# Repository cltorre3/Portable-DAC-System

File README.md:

# Portable-DAC-System
This is meant to be the repository for all the major electrical files for the portable DAC system.
The ESP32s are programmed in Arduino and the PCB was built in KiCAD

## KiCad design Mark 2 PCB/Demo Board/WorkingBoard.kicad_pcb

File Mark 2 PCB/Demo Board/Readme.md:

This will serve as the location for the demonstration board backup

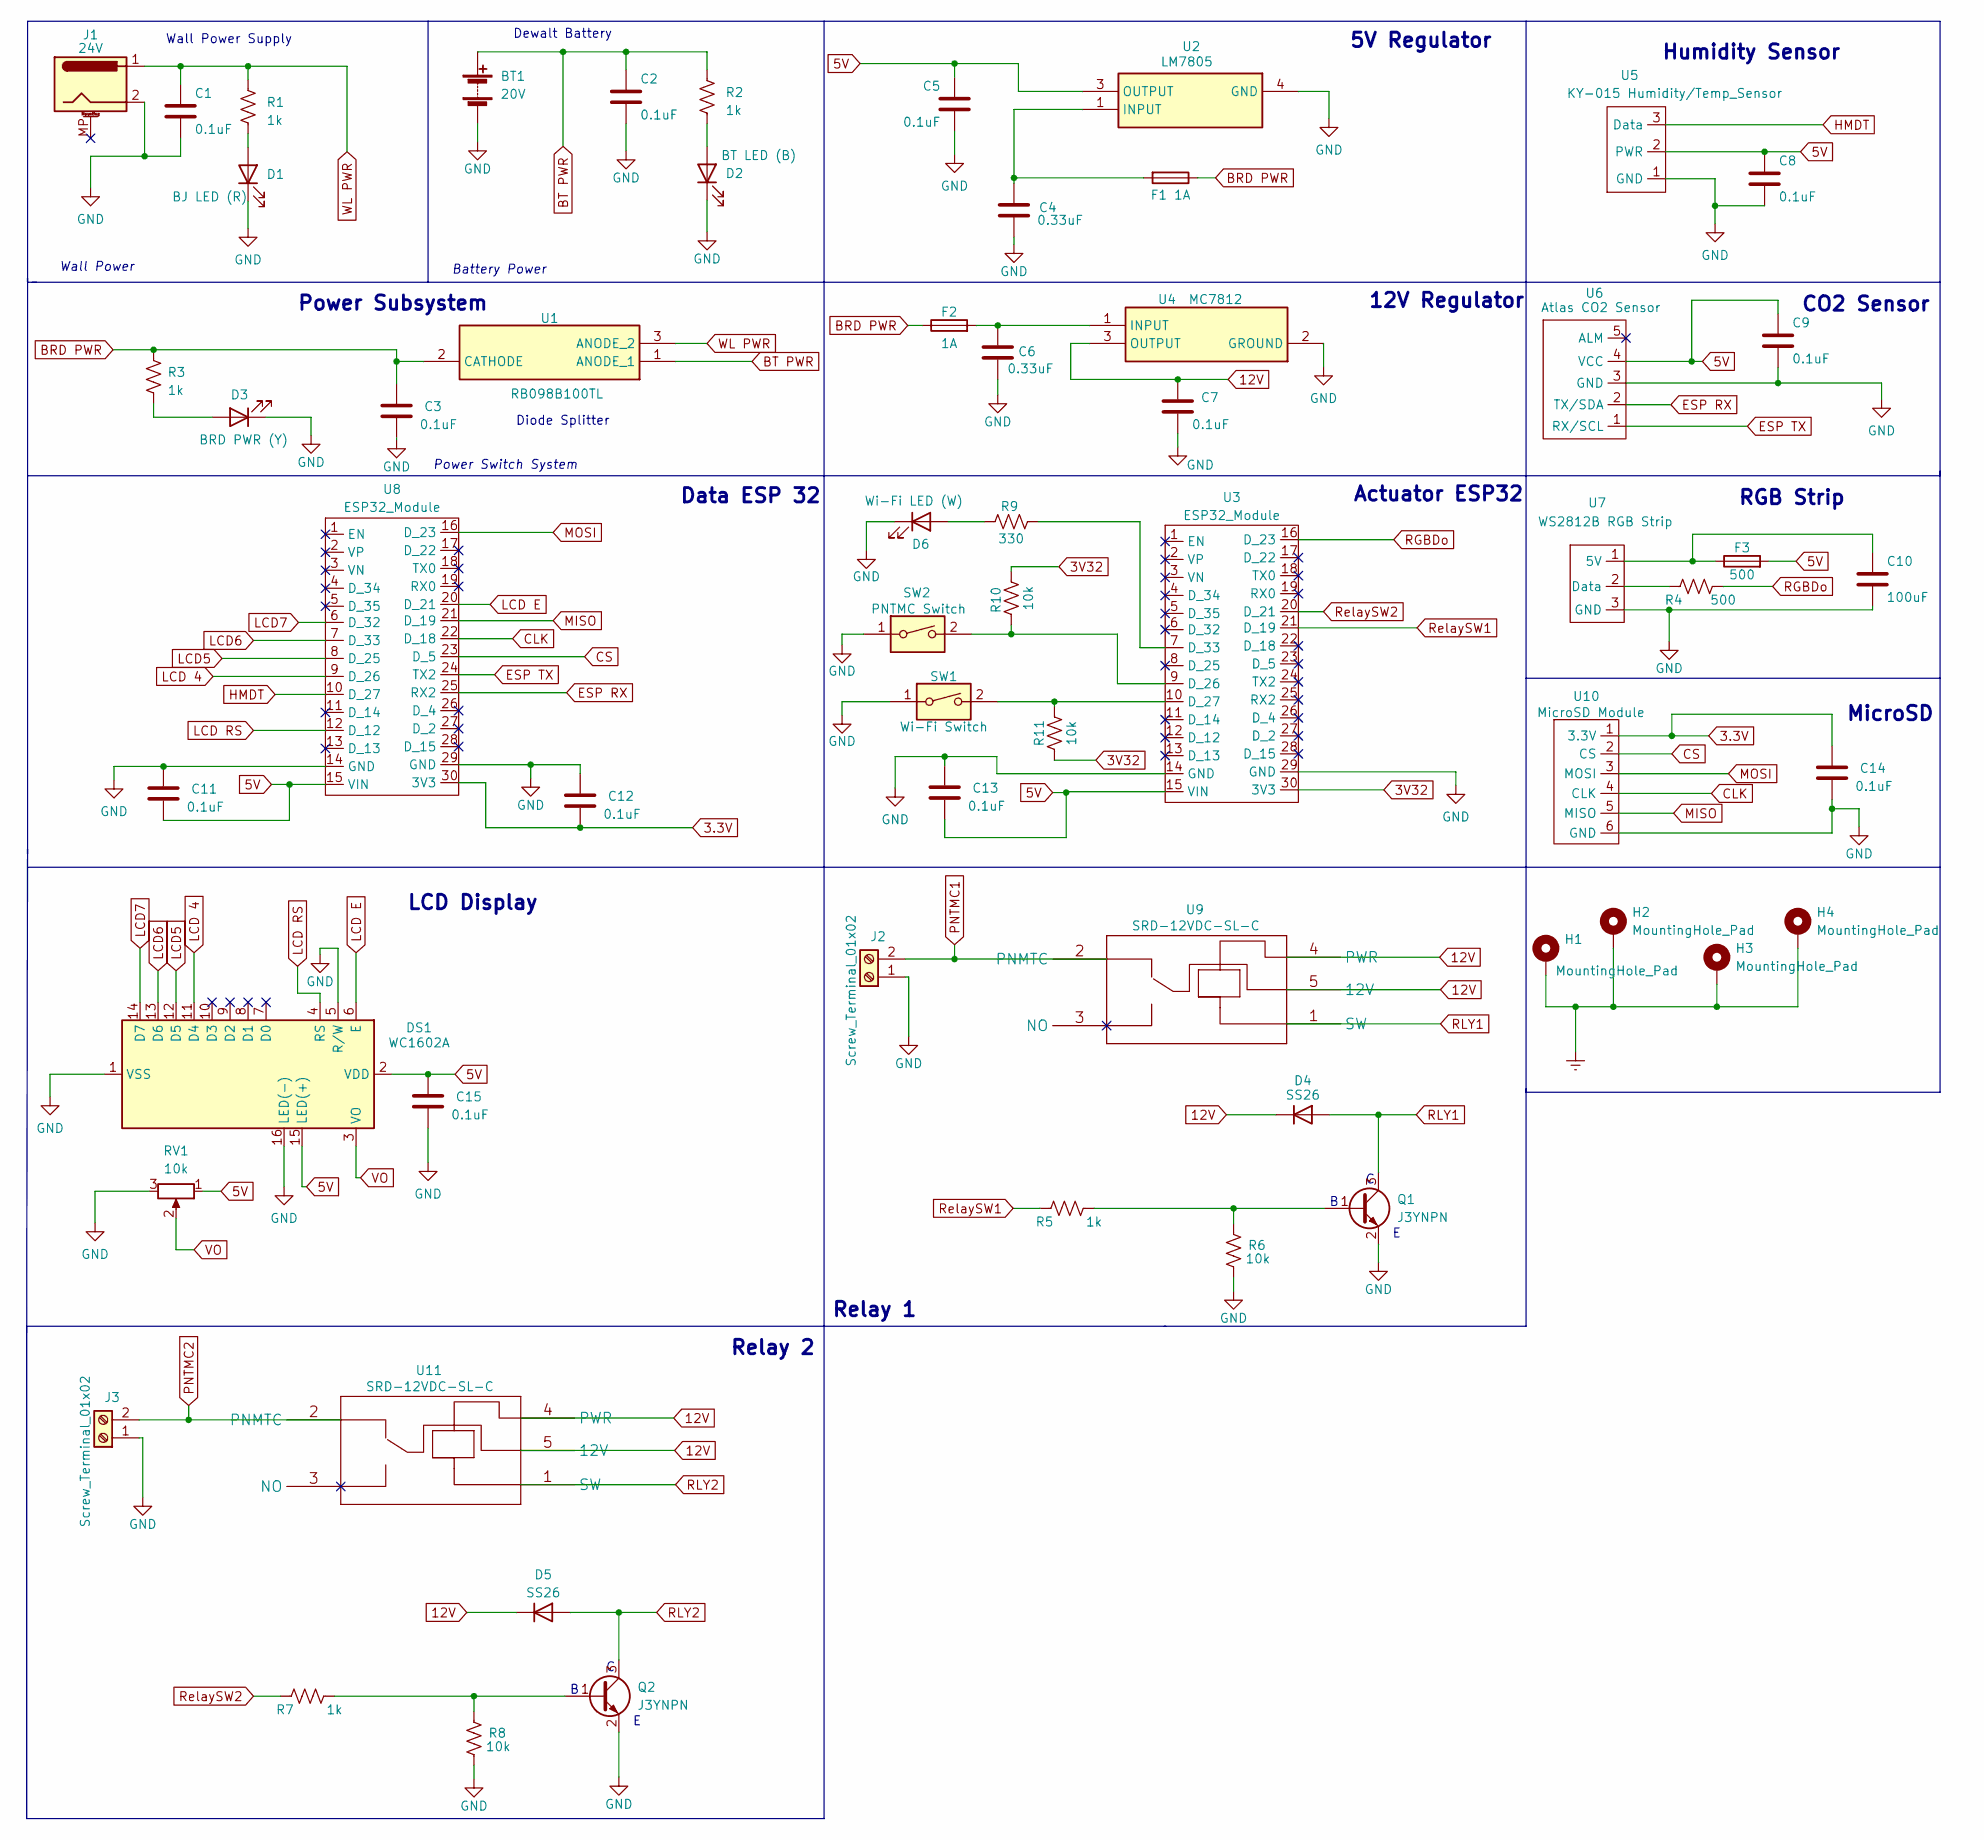
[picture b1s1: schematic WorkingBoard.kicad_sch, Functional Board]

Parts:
BT1: 20V; TerminalBlock_TE_282834-2_1x02_P2.54mm_Horizontal
C1, C2, C3, C5, C7, C8, C9, C11, C12, C13, C14, C15: 0.1uF; C_0805_2012Metric
C4, C6: 0.33uF; C_0805_2012Metric
C10: 100uF; C_0805_2012Metric
D1: BJ LED (R); LED_0805_2012Metric
D2: BT LED (B); LED_0805_2012Metric
D3: BRD PWR (Y); LED_0805_2012Metric
D4, D5: SS26
D6: Wi-Fi LED (W); LED_0805_2012Metric
DS1: WC1602A
F1, F2: 1A; Fuseholder_Cylinder-5x20mm_Schurter_0031_8201_Horizontal_Op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
F3: 500; Fuseholder_Cylinder-5x20mm_Schurter_0031_8201_Horizontal_Op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
H1, H2, H3, H4: MountingHole_Pad; MountingHole_3mm_Pad
J1: 24V; BarrelJack_Horizontal
J2, J3: Screw_Terminal_01x02; TerminalBlock_TE_282834-2_1x02_P2.54mm_Horizontal
Q1, Q2: J3YNPN; SOT-23
R1, R2, R3, R5, R7: 1k; R_0805_2012Metric
R4: 500; R_0805_2012Metric
R6, R8, R10, R11: 10k; R_0805_2012Metric
R9: 330; R_0805_2012Metric
RV1: 10k; Potentiometer_Bourns_3266Y_Vertical
SW1: Wi-Fi Switch; PinHeader_1x02_P2.54mm_Vertical
SW2: PNTMC Switch; PinHeader_1x02_P2.54mm_Vertical
U1: RB098B100TL; diodeSwitch
U2: LM7805
U3, U8: ESP32_Module; ESP32DevKit
U4: MC7812
U5: KY-015 Humidity/Temp_Sensor; PinHeader_1x03_P2.54mm_Horizontal
U6: Atlas CO2 Sensor; PinHeader_1x05_P2.54mm_Horizontal
U7: WS2812B RGB Strip; PinHeader_1x03_P2.54mm_Horizontal
U9, U11: SRD-12VDC-SL-C; SRD Relay
U10: MicroSD Module; PinHeader_1x06_P2.54mm_Vertical

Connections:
3.3V: C12.2, C14.1, U8.30 (3V3), U10.1 (3.3V)
3V32: R10.2, R11.1, U3.30 (3V3)
5V: C5.1, C8.1, C9.1, C11.2, C13.2, C15.1, DS1.2 (VDD), DS1.15 (LED(+)), F3.2, RV1.1, U2.3 (OUTPUT), U3.15 (VIN), U5.2 (PWR), U6.4 (VCC), U8.15 (VIN)
12V: C7.1, D4.1 (K), D5.1 (K), U4.3 (OUTPUT), U9.4 (PWR), U9.5 (12V), U11.4 (PWR), U11.5 (12V)
BT PWR: BT1.1 (+), C2.1, R2.1, U1.1 (ANODE_1)
CLK: U8.22 (D_18), U10.4 (CLK)
CS: U8.23 (D_5), U10.2 (CS)
ESP RX: U6.2 (TX/SDA), U8.25 (RX2)
ESP TX: U6.1 (RX/SCL), U8.24 (TX2)
Earth: H1.1, H2.1, H3.1, H4.1
GND: BT1.2 (-), C1.2, C2.2, C3.2, C4.2, C5.2, C6.2, C7.2, C8.2, C9.2, C10.2, C11.1, C12.1, C13.1, C14.2, C15.2, D1.1 (K), D2.1 (K), D3.1 (K), D6.1 (K), DS1.1 (VSS), DS1.5 (R/W), DS1.16 (LED(-)), J1.2, J2.1, J3.1, Q1.2 (E), Q2.2 (E), R6.1, R8.1, RV1.3, SW1.1, SW2.1, U2.4 (GND), U3.14 (GND), U3.29 (GND), U4.2 (GROUND), U5.1 (GND), U6.3 (GND), U7.3 (GND), U8.14 (GND), U8.29 (GND), U10.6 (GND)
HMDT: U5.3 (Data), U8.10 (D_27)
LCD5: DS1.12 (D5), U8.8 (D_25)
LCD6: DS1.13 (D6), U8.7 (D_33)
LCD7: DS1.14 (D7), U8.6 (D_32)
LCD 4: DS1.11 (D4), U8.9 (D_26)
LCD E: DS1.6 (E), U8.20 (D_21)
LCD RS: DS1.4 (RS), U8.12 (D_12)
MISO: U8.21 (D_19), U10.5 (MISO)
MOSI: U8.16 (D_23), U10.3 (MOSI)
unnamed: D1.2 (A), R1.2
unnamed: D2.2 (A), R2.2
unnamed: D3.2 (A), R3.2
unnamed: D6.2 (A), R9.1
unnamed: Q1.1 (B), R5.2, R6.2
unnamed: Q2.1 (B), R7.2, R8.2
unnamed: C4.1, F1.2, U2.1 (INPUT)
unnamed: R10.1, SW2.2, U3.9 (D_26)
unnamed: R11.2, SW1.2, U3.10 (D_27)
unnamed: R9.2, U3.7 (D_33)
unnamed: C6.1, F2.2, U4.1 (INPUT)
unnamed: C10.1, F3.1, U7.1 (5V)
unnamed: R4.1, U7.2 (Data)
PNTMC1: J2.2, U9.2 (PNMTC)
PNTMC2: J3.2, U11.2 (PNMTC)
RGBDo: R4.2, U3.16 (D_23)
RLY1: D4.2 (A), Q1.3 (C), U9.1 (SW)
RLY2: D5.2 (A), Q2.3 (C), U11.1 (SW)
RelaySW1: R5.1, U3.21 (D_19)
RelaySW2: R7.1, U3.20 (D_21)
VO: DS1.3 (VO), RV1.2

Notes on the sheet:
5V Regulator
Actuator ESP32
Data ESP 32
MicroSD
Wall Power
Dewalt Battery
Battery Power
RGB Strip
CO2 Sensor
Diode Splitter
Humidity Sensor
Wall Power Supply
Power Subsystem
Relay 2
Power Switch System
12V Regulator
Relay 1
LCD Display

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
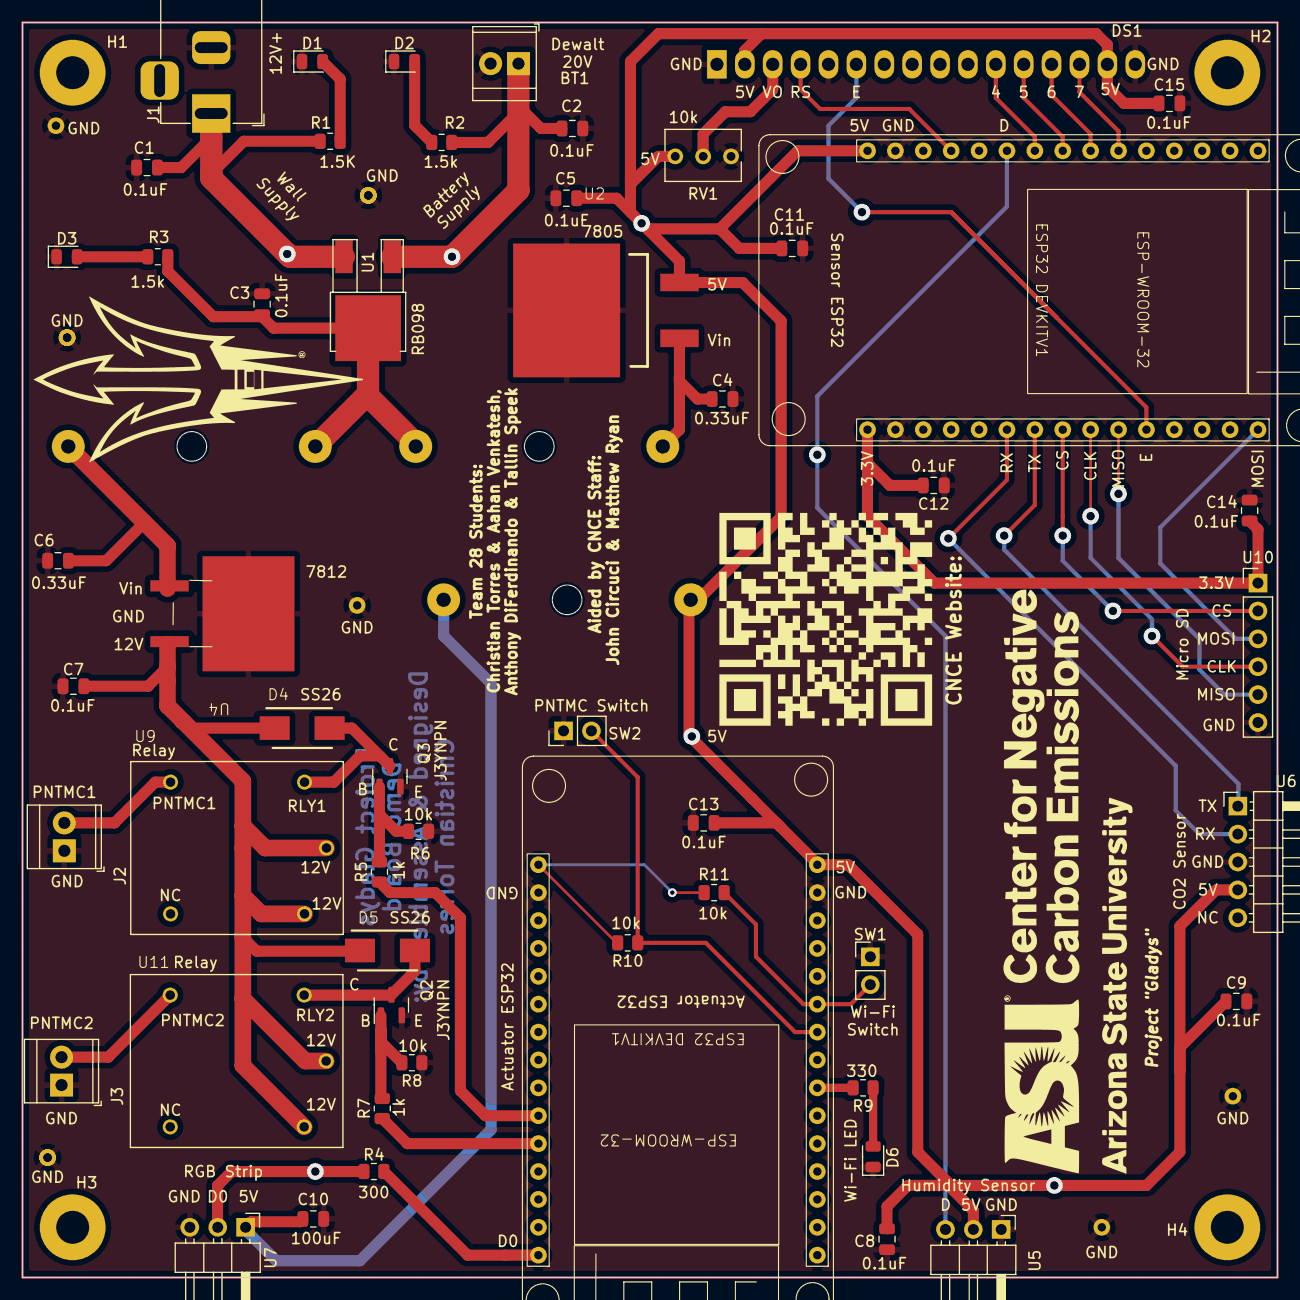
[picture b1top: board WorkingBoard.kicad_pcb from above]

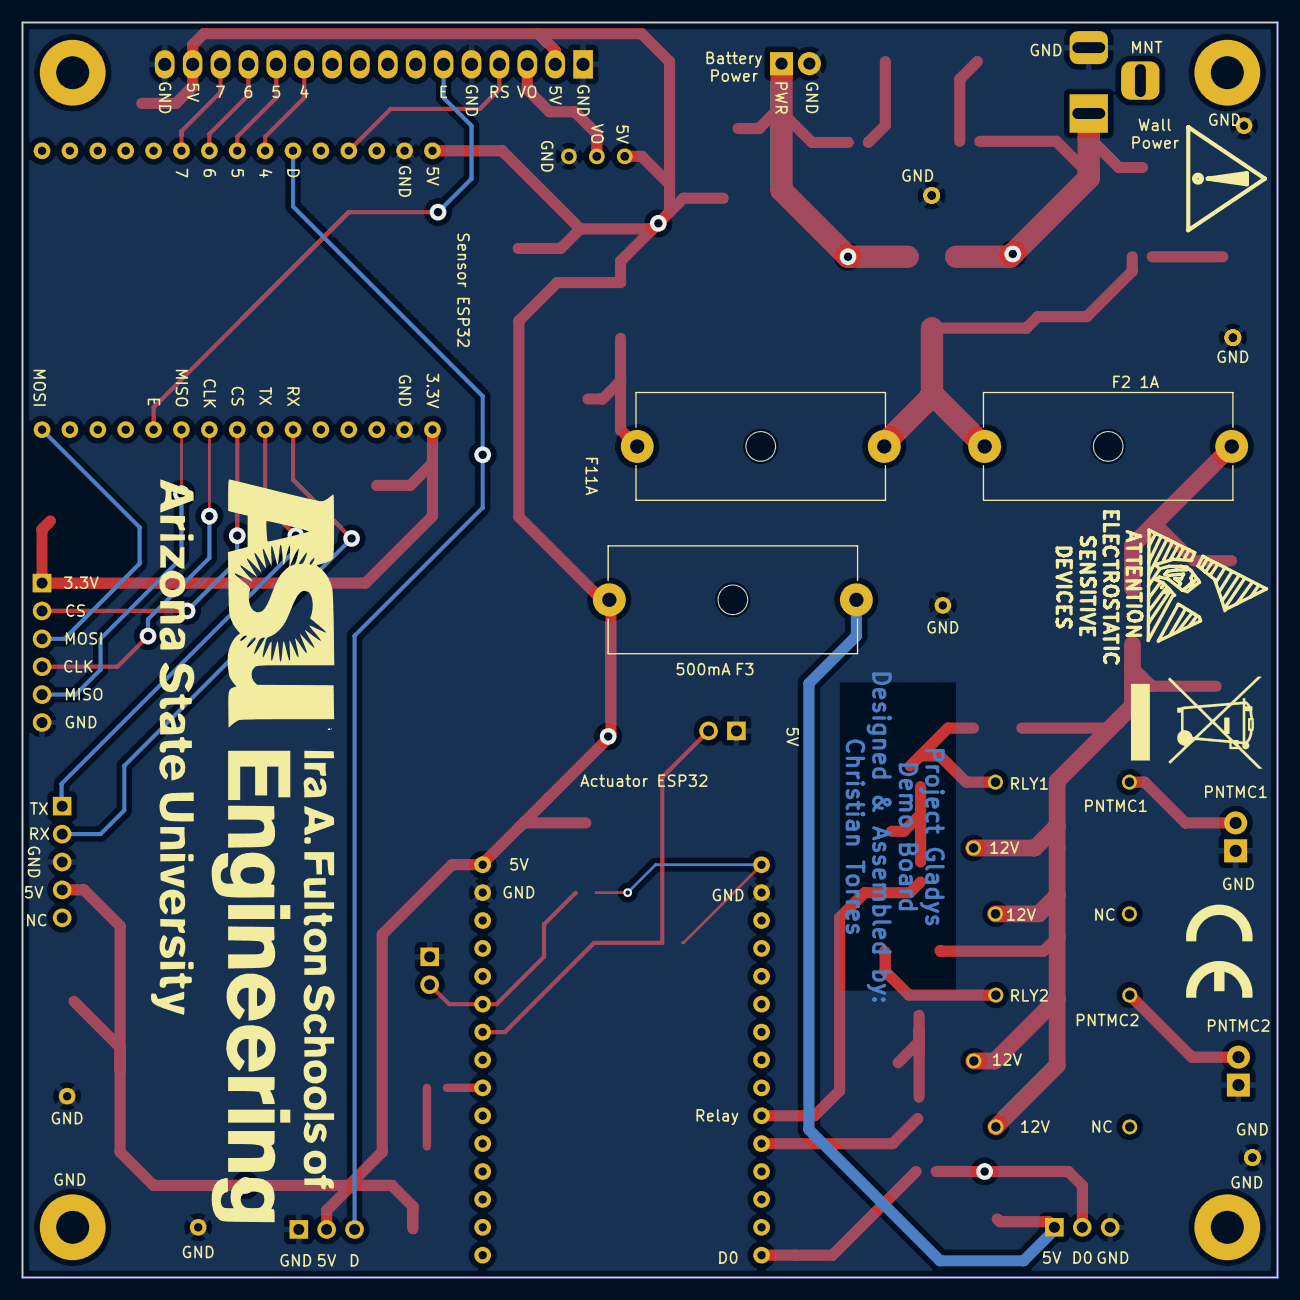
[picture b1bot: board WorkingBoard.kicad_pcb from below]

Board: 2 copper layers, 114.3 x 114.3 mm, 60 parts (4 on the bottom side), 43 nets.

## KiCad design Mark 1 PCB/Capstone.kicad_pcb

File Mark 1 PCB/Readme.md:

This folder will hold all the files available for the original capstone PCB made in Janurary

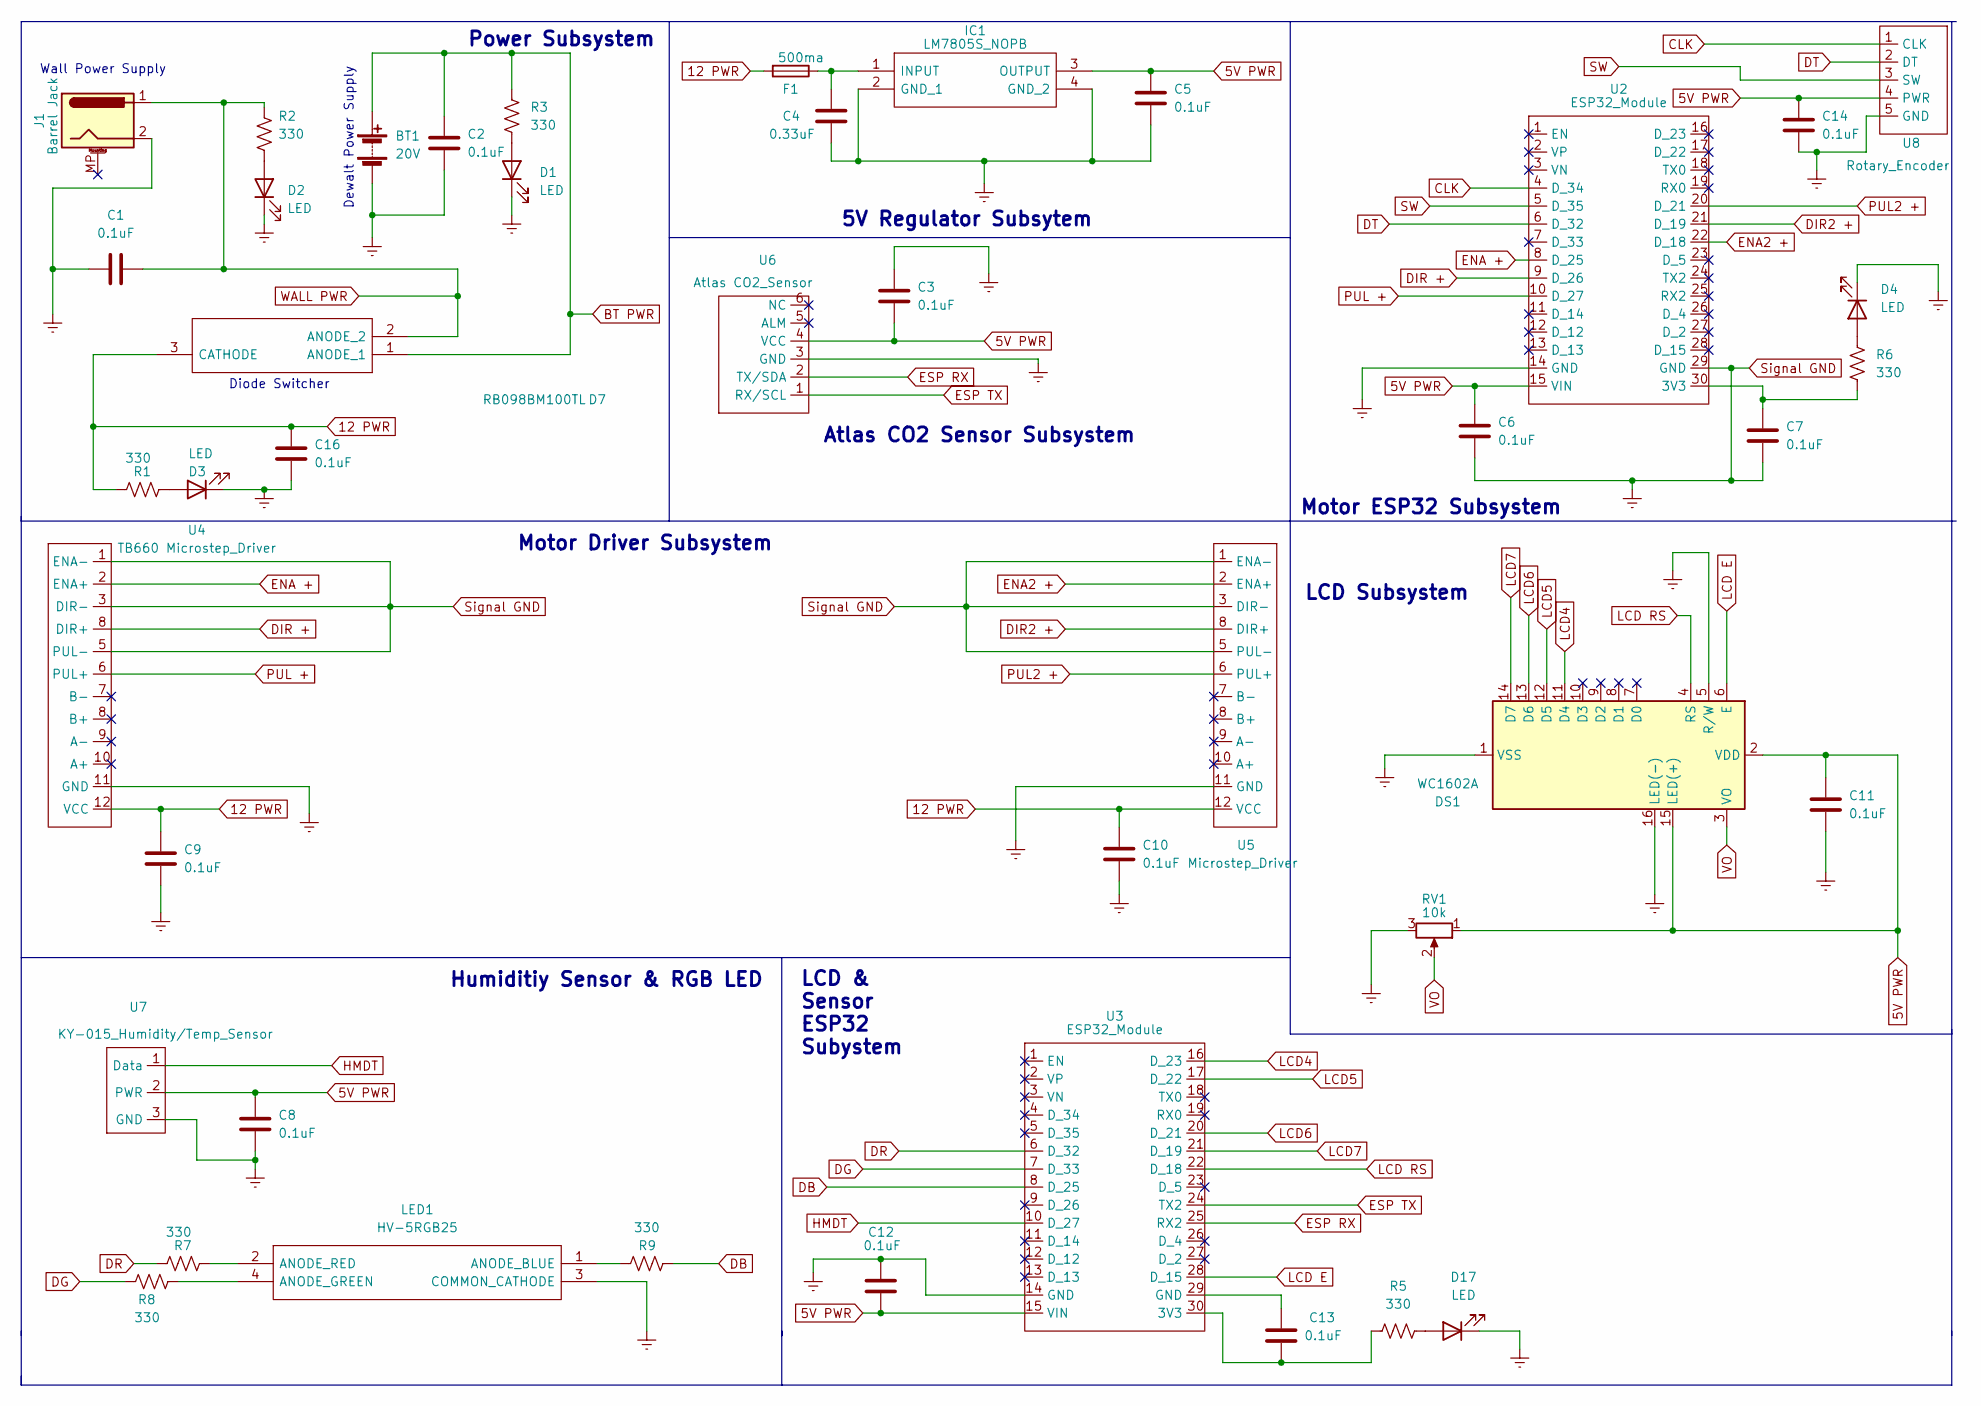
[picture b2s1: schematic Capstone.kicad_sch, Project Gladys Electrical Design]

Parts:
BT1: 20V; TerminalBlock_TE_282834-2_1x02_P2.54mm_Horizontal
C1, C2, C3, C5, C6, C7, C8, C9, C10, C11, C12, C13, C14, C16: 0.1uF; LED_0805_2012Metric
C4: 0.33uF; LED_0805_2012Metric
D1, D2, D3, D4, D17: LED; LED_0805_2012Metric
D7: RB098BM100TL; RB098BM100FHTL; Mouser Part Number 755-RB098BM100TL
DS1: WC1602A
F1: 500ma; Fuseholder_Cylinder-5x20mm_Schurter_0031_8201_Horizontal_Op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
IC1: LM7805S_NOPB; KTT0003B; Mouser Part Number 595-LM7805S/NOPB
J1: Barrel Jack; BarrelJack_Horizontal
LED1: HV-5RGB25; HV5RGB25; Mouser Part Number 743-HV-5RGB25
R1, R2, R3, R5, R6, R7, R8, R9: 330; R_0805_2012Metric
RV1: 10k; Potentiometer_Bourns_3266Y_Vertical
U2, U3: ESP32_Module; ESP32 Module
U4: TB660 Microstep_Driver; TerminalBlock_TE_1-282834-2_1x12_P2.54mm_Horizontal
U5: Microstep_Driver; TerminalBlock_TE_1-282834-2_1x12_P2.54mm_Horizontal
U6: Atlas CO2_Sensor; PinHeader_1x06_P2.54mm_Horizontal
U7: KY-015_Humidity/Temp_Sensor; PinHeader_1x03_P2.54mm_Horizontal
U8: Rotary_Encoder; PinHeader_1x05_P2.54mm_Vertical

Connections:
5V PWR: C3.1, C5.2, C6.2, C8.2, C11.2, C12.1, C14.2, DS1.2 (VDD), DS1.15 (LED(+)), IC1.3 (OUTPUT), RV1.1, U2.15 (VIN), U3.15 (VIN), U6.4 (VCC), U7.2 (PWR), U8.4 (PWR)
12 PWR: C9.2, C10.2, C16.2, D7.3 (CATHODE), F1.2, R1.1, U4.12 (VCC), U5.12 (VCC)
BT PWR: BT1.1 (+), C2.2, D7.1 (ANODE_1), R3.1
CLK: U2.4 (D_34), U8.1 (CLK)
DB: R9.1, U3.8 (D_25)
DG: R8.1, U3.7 (D_33)
DIR2 +: U2.21 (D_19), U5.8 (DIR+)
DIR +: U2.9 (D_26), U4.8 (DIR+)
DR: R7.1, U3.6 (D_32)
DT: U2.6 (D_32), U8.2 (DT)
ENA2 +: U2.22 (D_18), U5.2 (ENA+)
ENA +: U2.8 (D_25), U4.2 (ENA+)
ESP RX: U3.25 (RX2), U6.2 (TX/SDA)
ESP TX: U3.24 (TX2), U6.1 (RX/SCL)
HMDT: U3.10 (D_27), U7.1 (Data)
LCD4: DS1.11 (D4), U3.16 (D_23)
LCD5: DS1.12 (D5), U3.17 (D_22)
LCD6: DS1.13 (D6), U3.20 (D_21)
LCD7: DS1.14 (D7), U3.21 (D_19)
LCD E: DS1.6 (E), U3.28 (D_15)
LCD RS: DS1.4 (RS), U3.22 (D_18)
unnamed: C4.2, F1.1, IC1.1 (INPUT)
unnamed: C7.2, R6.1, U2.30 (3V3)
unnamed: C13.1, R5.1, U3.30 (3V3)
unnamed: C13.2, U3.29 (GND)
unnamed: D1.2 (A), R3.2
unnamed: D2.2 (A), R2.2
unnamed: D3.2 (A), R1.2
unnamed: D4.2 (A), R6.2
unnamed: D17.2 (A), R5.2
unnamed: LED1.1 (ANODE_BLUE), R9.2
unnamed: LED1.2 (ANODE_RED), R7.2
unnamed: LED1.4 (ANODE_GREEN), R8.2
PUL2 +: U2.20 (D_21), U5.6 (PUL+)
PUL +: U2.10 (D_27), U4.6 (PUL+)
SW: U2.5 (D_35), U8.3 (SW)
Signal GND: BT1.2 (-), C1.1, C2.1, C3.2, C4.1, C5.1, C6.1, C7.1, C8.1, C9.1, C10.1, C11.1, C12.2, C14.1, C16.1, D1.1 (K), D2.1 (K), D3.1 (K), D4.1 (K), D17.1 (K), DS1.1 (VSS), DS1.5 (R/W), DS1.16 (LED(-)), IC1.2 (GND_1), IC1.4 (GND_2), J1.2, LED1.3 (COMMON_CATHODE), RV1.3, U2.14 (GND), U2.29 (GND), U3.14 (GND), U4.1 (ENA-), U4.3 (DIR-), U4.5 (PUL-), U4.11 (GND), U5.1 (ENA-), U5.3 (DIR-), U5.5 (PUL-), U5.11 (GND), U6.3 (GND), U7.3 (GND), U8.5 (GND)
VO: DS1.3 (VO), RV1.2
WALL PWR: C1.2, D7.2 (ANODE_2), J1.1, R2.1

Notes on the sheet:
Motor ESP32 Subsystem
Dewalt Power Supply
LCD & Sensor ESP32 Subystem
5V Regulator Subsytem
Atlas CO2 Sensor Subsystem
Power Subsystem
Humiditiy Sensor & RGB LED
Diode Switcher
LCD Subsystem
Motor Driver Subsystem
Wall Power Supply

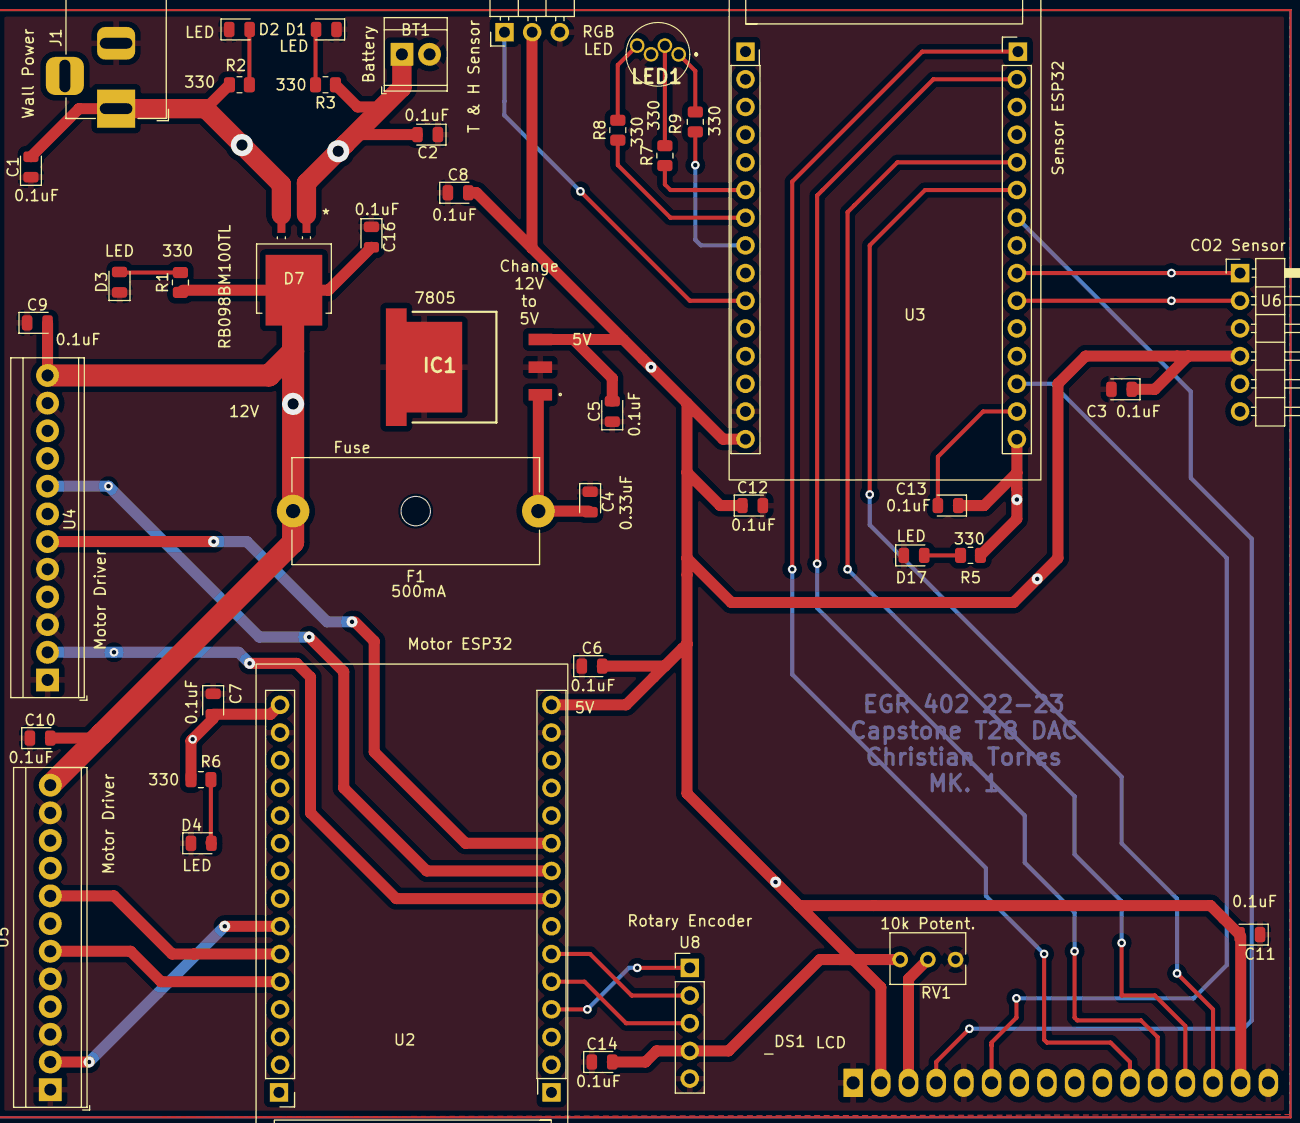
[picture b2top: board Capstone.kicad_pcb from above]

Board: 2 copper layers, 43 parts (0 on the bottom side), 39 nets.

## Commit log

2023-05-03 Rename TotalCode.ino to HumidityLCDino
2023-05-03 Create IOTlogininfo,txt

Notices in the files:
parts and their libraries:
Copyright 2021 Accelerated Designs. All rights reserved.
